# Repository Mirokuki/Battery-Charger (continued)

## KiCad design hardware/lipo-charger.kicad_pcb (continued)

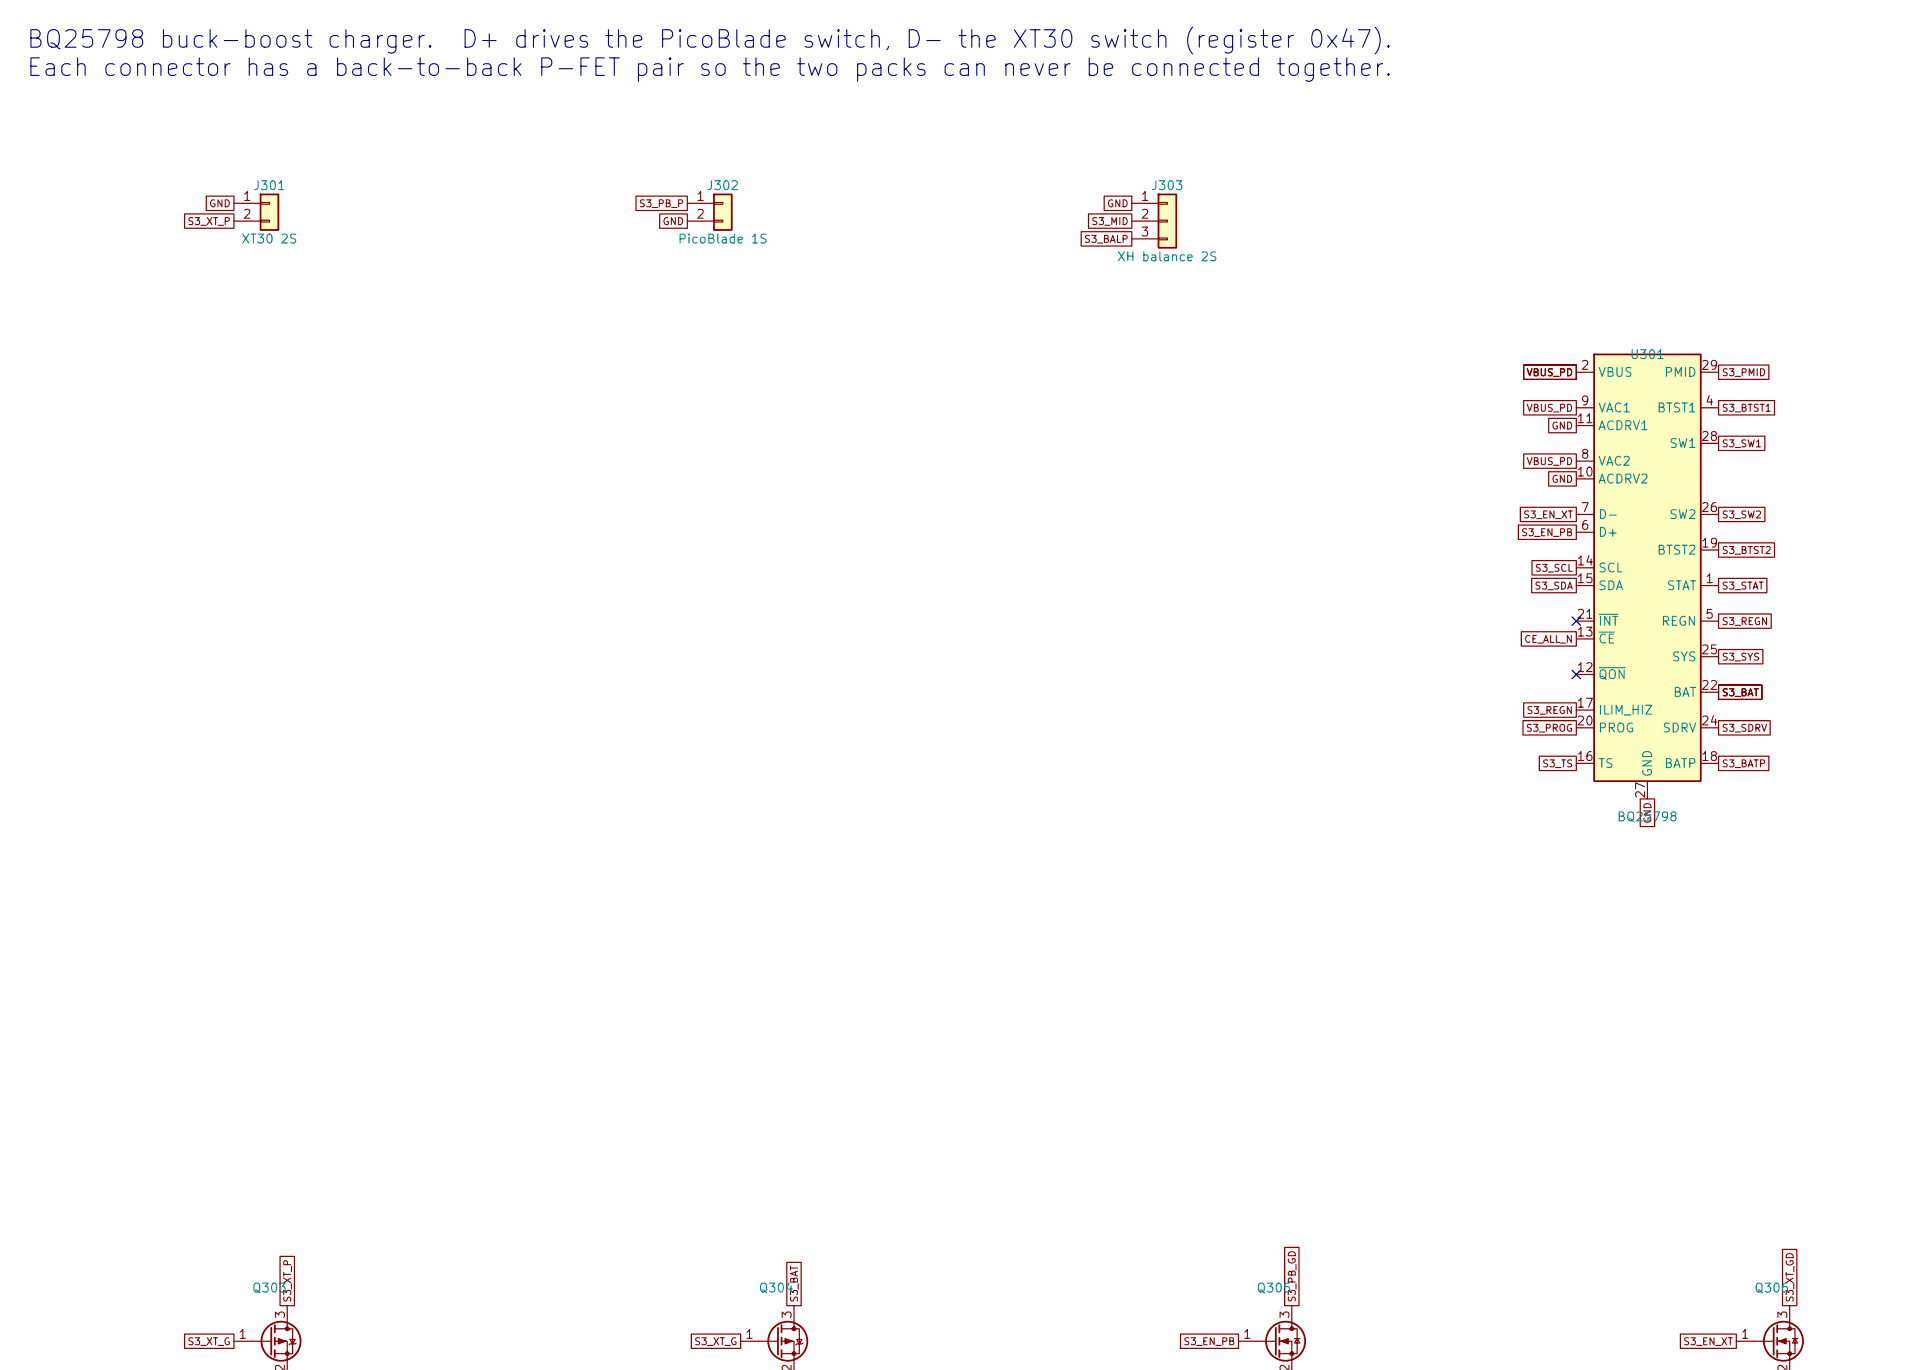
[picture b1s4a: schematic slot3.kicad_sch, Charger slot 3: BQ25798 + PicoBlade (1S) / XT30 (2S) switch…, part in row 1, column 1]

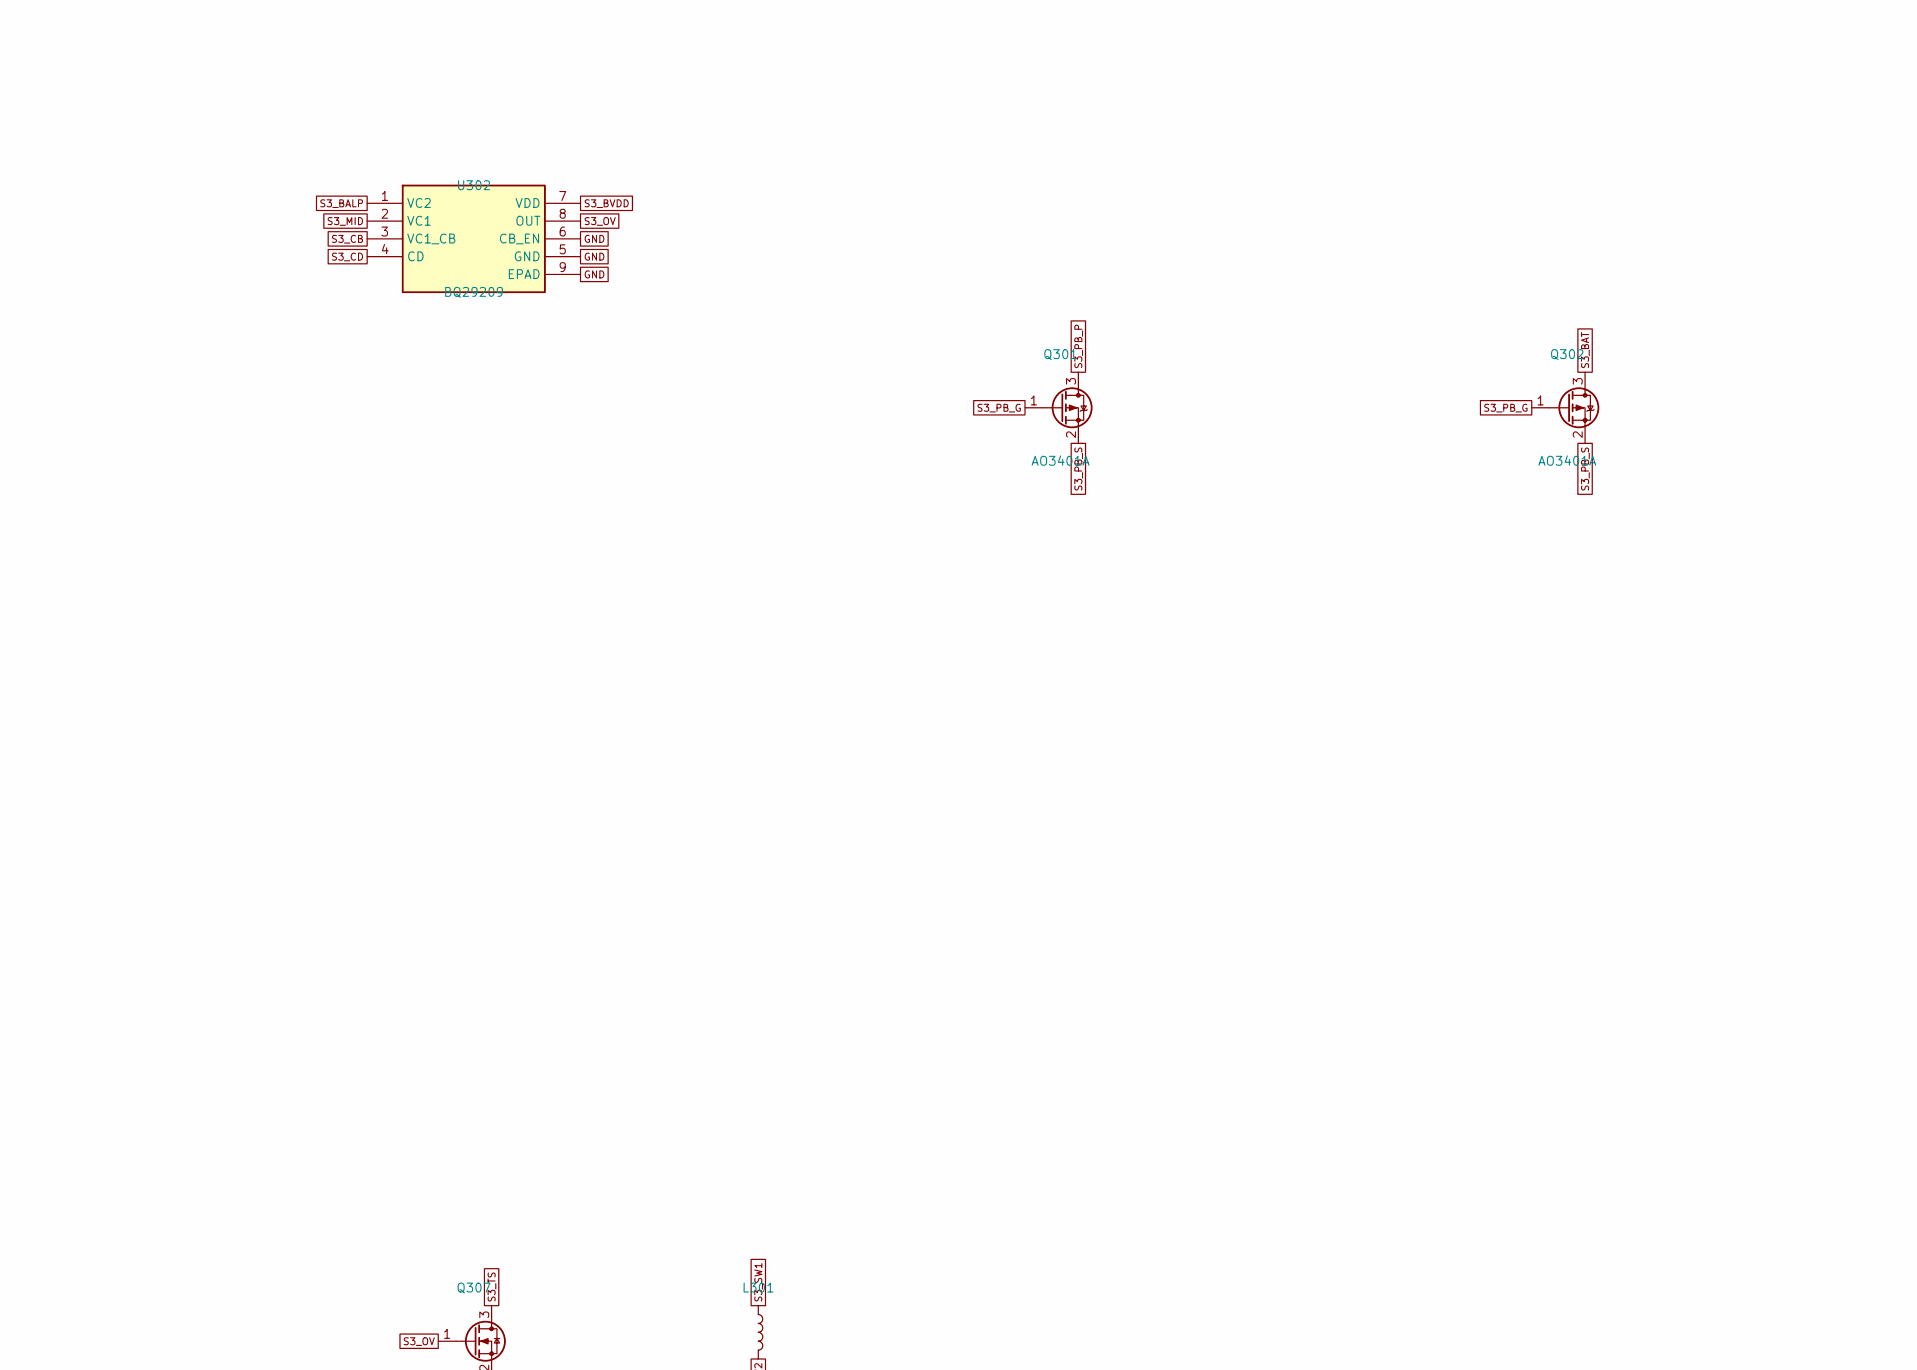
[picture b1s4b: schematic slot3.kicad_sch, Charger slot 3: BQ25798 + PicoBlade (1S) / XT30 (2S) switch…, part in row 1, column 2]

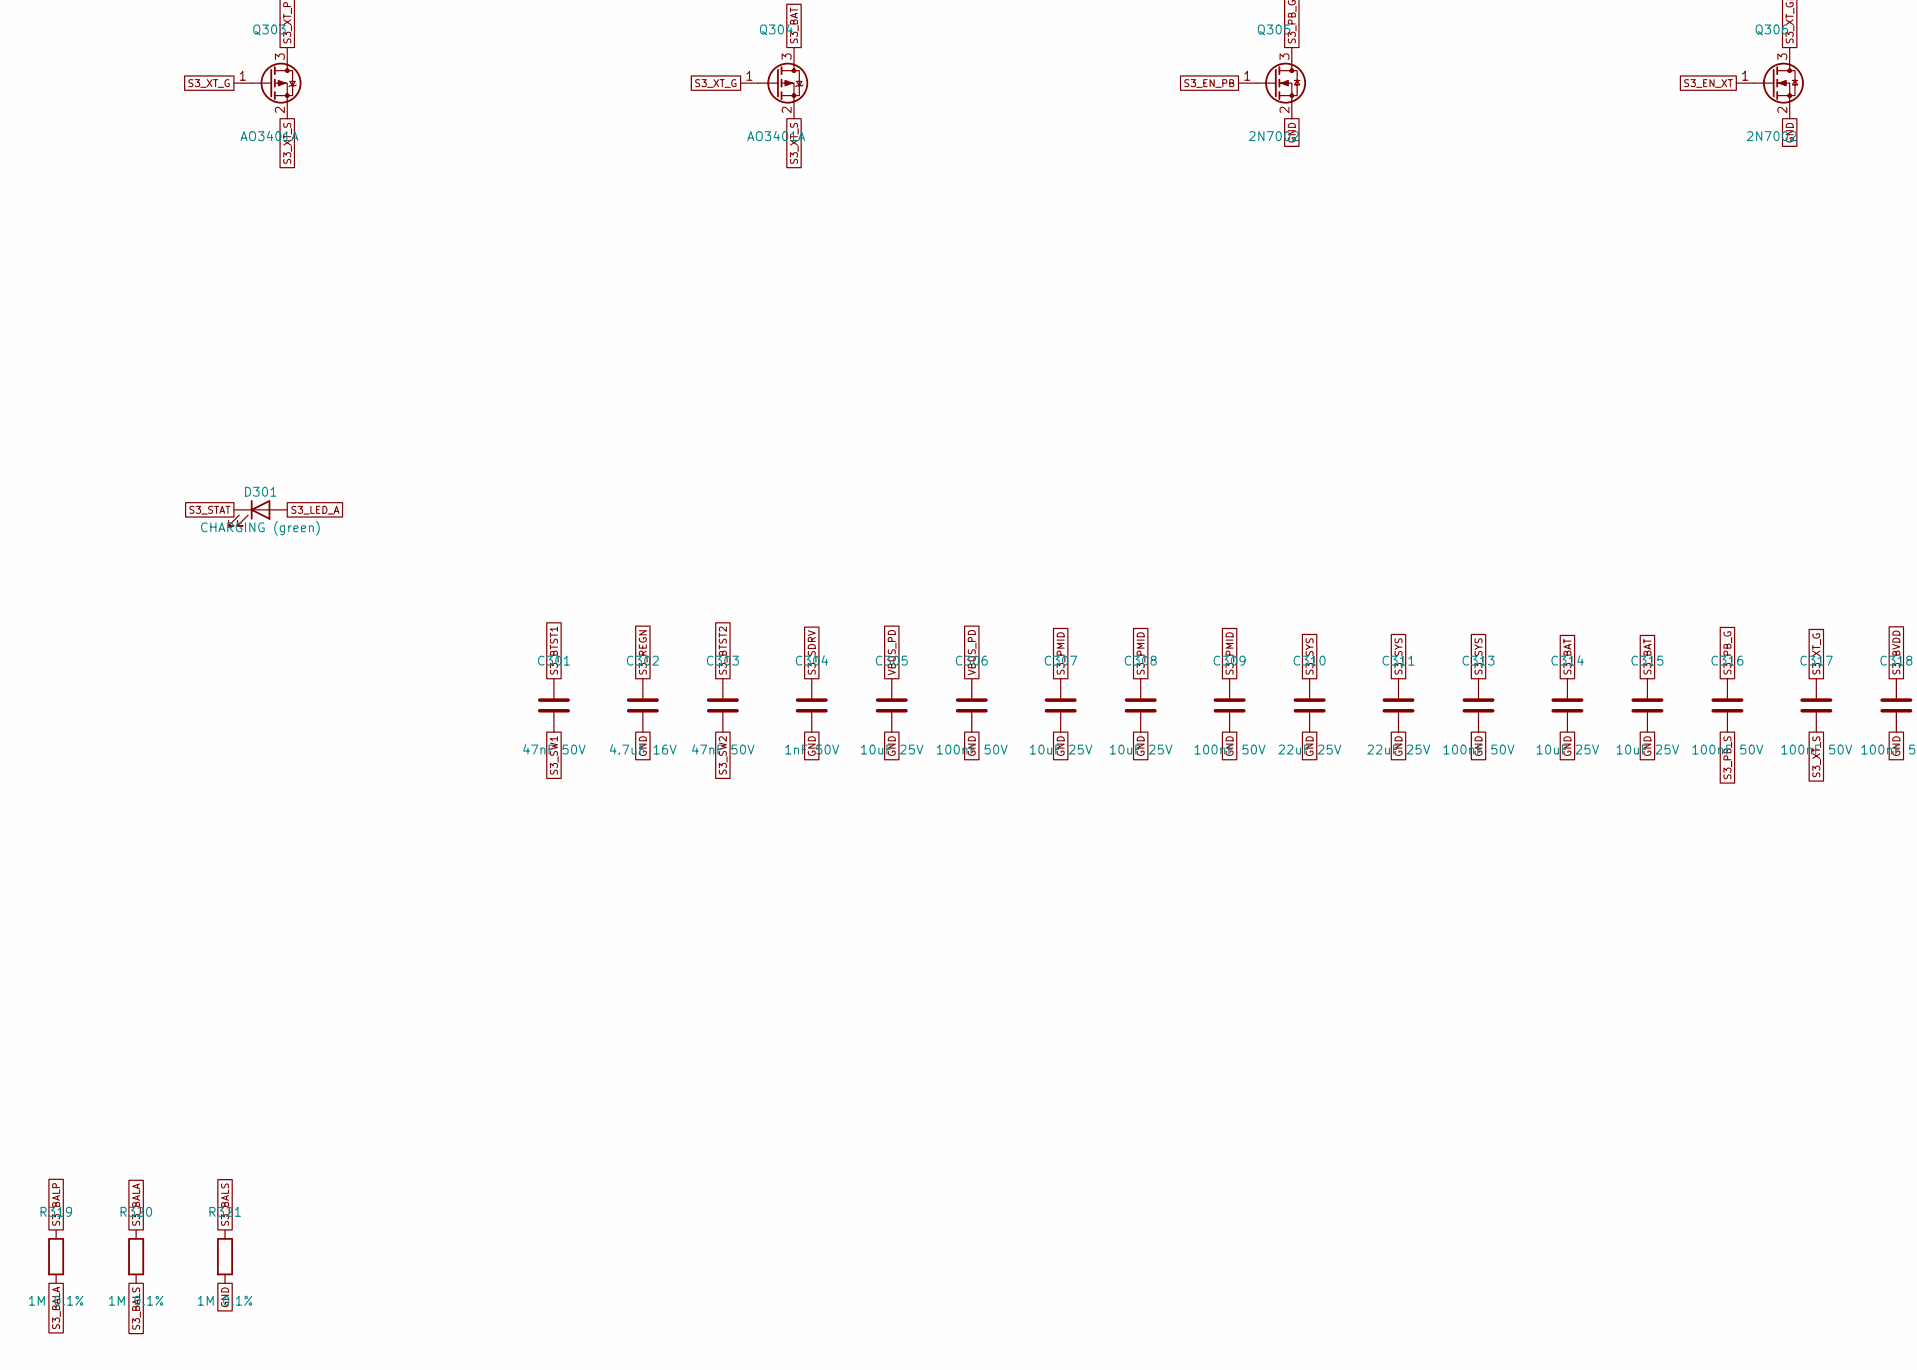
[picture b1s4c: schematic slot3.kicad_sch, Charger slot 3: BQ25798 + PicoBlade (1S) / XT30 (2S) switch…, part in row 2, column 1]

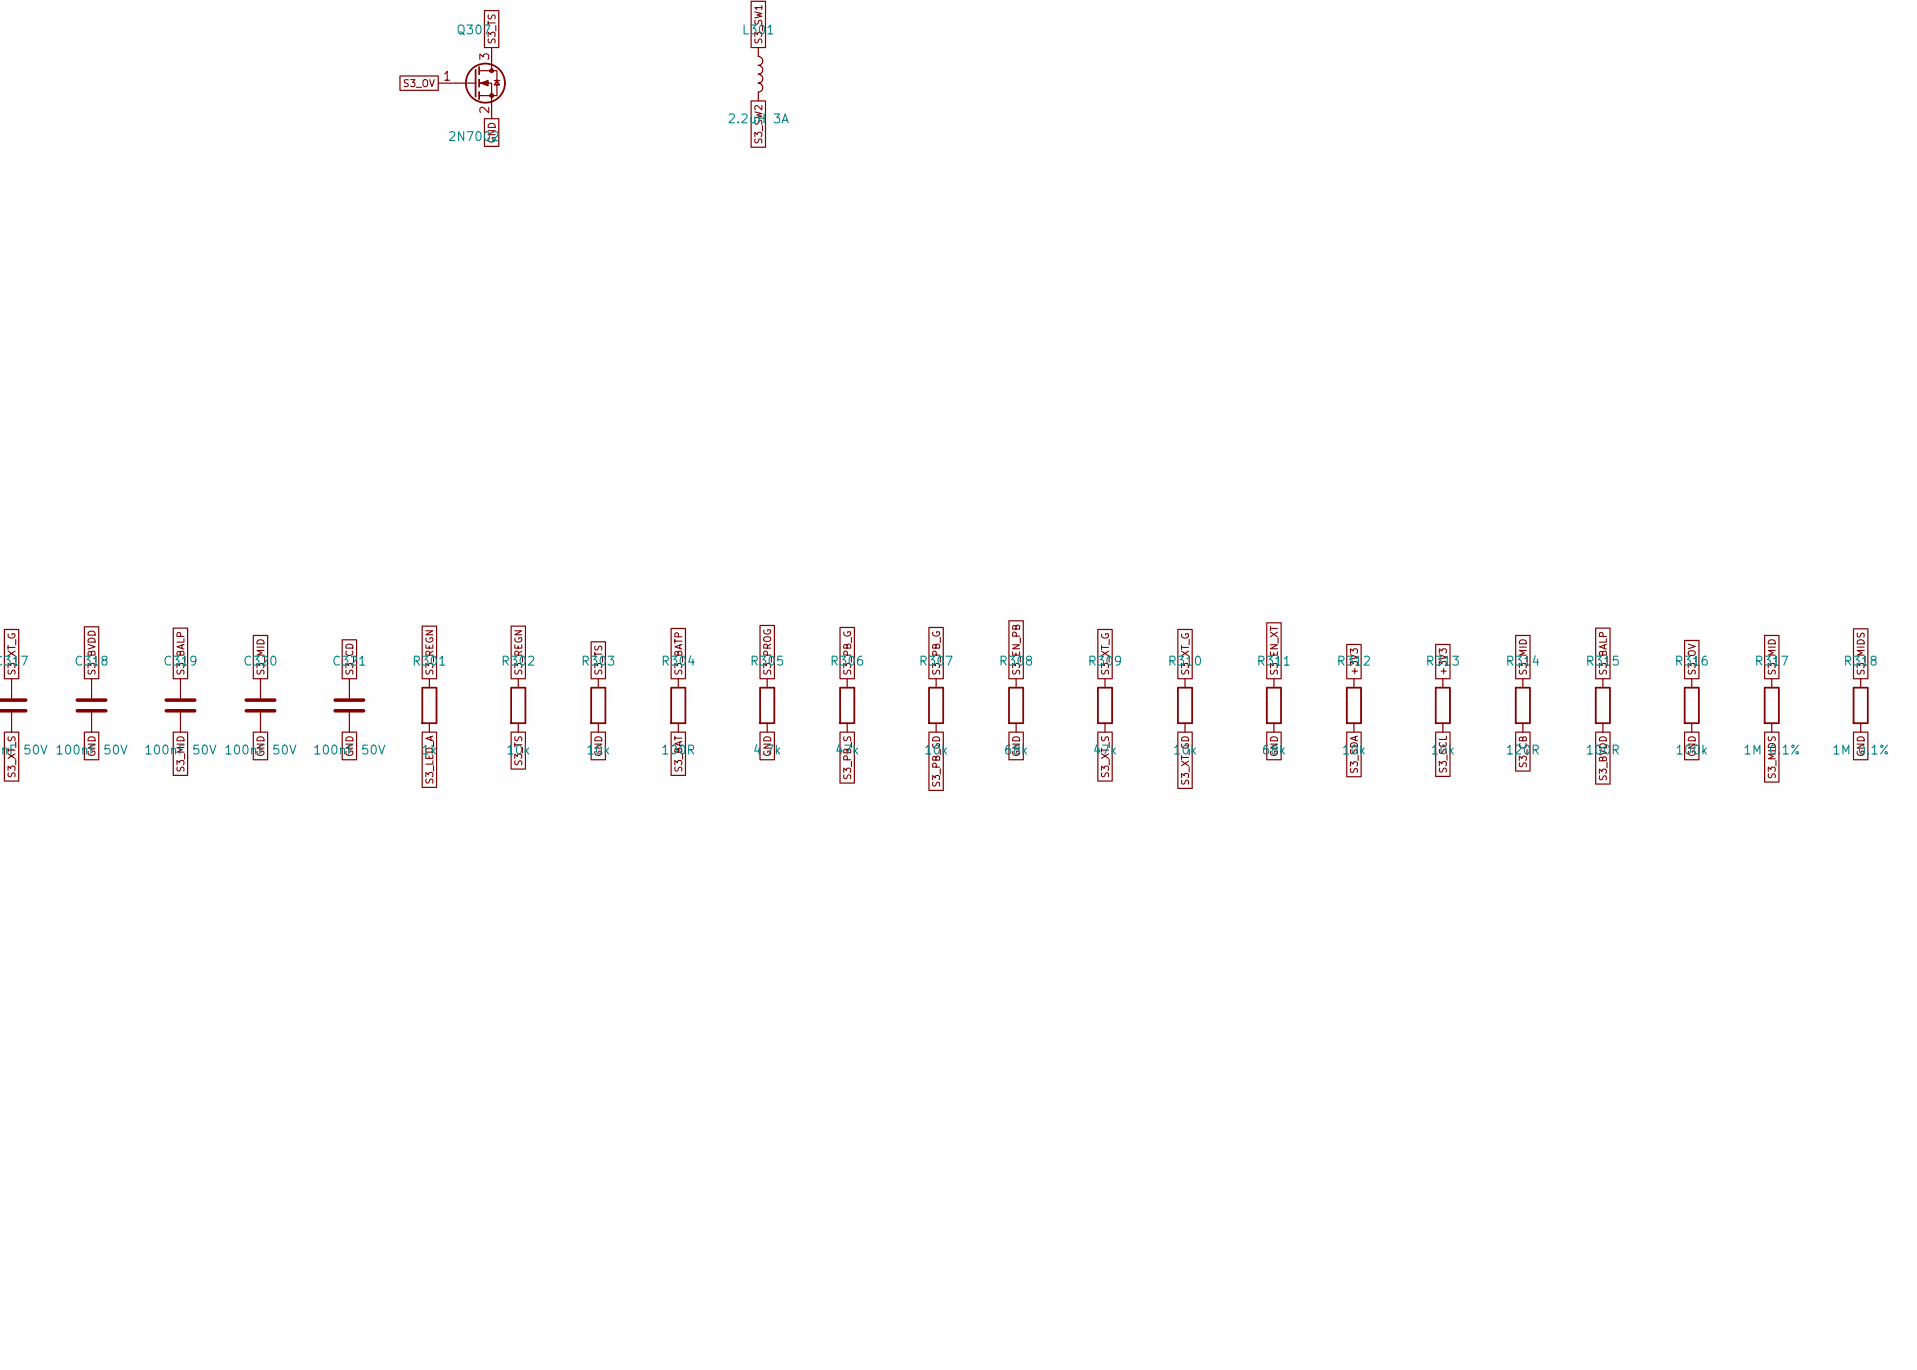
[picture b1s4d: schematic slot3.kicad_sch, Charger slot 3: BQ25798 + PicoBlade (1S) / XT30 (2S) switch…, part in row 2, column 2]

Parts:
C301, C303: 47nF 50V; C_0402_1005Metric; MPN CL05B473KB5NNNC
C302: 4.7uF 16V; C_0603_1608Metric; MPN CL10A475KO8NNNC; LCSC C19666
C304: 1nF 50V; C_0402_1005Metric; MPN CL05B102KB5NNNC; LCSC C1523
C305, C307, C308, C314, C315: 10uF 25V; C_0805_2012Metric; MPN CL21A106KAYNNNE; LCSC C15850
C306, C309, C313, C316, C317, C318, C319, C320, C321: 100nF 50V; C_0402_1005Metric; MPN CL05B104KB54PNC; LCSC C307331
C310, C311: 22uF 25V; C_0805_2012Metric; MPN CL21A226MAQNNNE; LCSC C45783
D301: CHARGING (green); LED_0603_1608Metric; MPN 19-217/GHC-YR1S2/3T; LCSC C72043
J301: XT30 2S; AMASS_XT30UPB-M_1x02_P5.0mm_Vertical; MPN XT30UPB-M; LCSC C99101
J302: PicoBlade 1S; Molex_PicoBlade_53047-0210_1x02_P1.25mm_Vertical; MPN 0530470210
J303: XH balance 2S; JST_XH_B3B-XH-A_1x03_P2.50mm_Vertical; MPN B3B-XH-A; LCSC C144394
L301: 2.2uH 3A; L_Changjiang_FNR4030S; MPN FNR4030S2R2MT
Q301, Q302, Q303, Q304: AO3401A; SOT-23; MPN AO3401A; LCSC C15127
Q305, Q306, Q307: 2N7002; SOT-23; MPN 2N7002; LCSC C8545
R301: 1k; R_0402_1005Metric; MPN 0402WGF1001TCE; LCSC C11702
R302, R303, R307, R310, R312, R313: 10k; R_0402_1005Metric; MPN 0402WGF1002TCE; LCSC C25744
R304, R315: 100R; R_0402_1005Metric; MPN 0402WGF1000TCE; LCSC C25076
R305: 4.7k; R_0402_1005Metric; MPN 0402WGF4701TCE; LCSC C25900
R306, R309: 47k; R_0402_1005Metric; MPN 0402WGF4702TCE; LCSC C25792
R308, R311: 68k; R_0402_1005Metric; MPN 0402WGF6802TCE; LCSC C36871
R314: 120R; R_0402_1005Metric; MPN 0402WGF1200TCE
R316: 100k; R_0402_1005Metric; MPN 0402WGF1003TCE; LCSC C25741
R317, R318, R319, R320, R321: 1M 0.1%; R_0402_1005Metric; MPN RT0402BRD071ML
U301: BQ25798; Texas_RQM0029A_VQFN-29_4x4mm_P0.4mm; MPN BQ25798RQMR; LCSC C2876768
U302: BQ29209; VSON-8-1EP_3x3mm_P0.65mm_EP1.65x2.4mm; MPN BQ29209DRBR

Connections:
+3V3: R312.1, R313.1; also elsewhere on the board
CE_ALL_N: U301.13 (~CE); also elsewhere on the board
GND: C302.2, C304.2, C305.2, C306.2, C307.2, C308.2, C309.2, C310.2, C311.2, C313.2, C314.2, C315.2, C318.2, C320.2, C321.2, J301.1, J302.2, J303.1, Q305.2 (S), Q306.2 (S), Q307.2 (S), R303.2, R305.2, R308.2, R311.2, R316.2, R318.2, R321.2, U301.10 (ACDRV2), U301.11 (ACDRV1), U301.27 (GND), U302.5 (GND), U302.6 (CB_EN), U302.9 (EPAD); also elsewhere on the board
S3_BALA: R319.2, R320.1
S3_BALP: C319.1, J303.3, R315.1, R319.1, U302.1 (VC2)
S3_BALS: R320.2, R321.1; also elsewhere on the board
S3_BAT: C314.1, C315.1, Q302.3 (D), Q304.3 (D), R304.2, U301.22 (BAT), U301.23 (BAT)
S3_BATP: R304.1, U301.18 (BATP)
S3_BTST1: C301.1, U301.4 (BTST1)
S3_BTST2: C303.1, U301.19 (BTST2)
S3_BVDD: C318.1, R315.2, U302.7 (VDD)
S3_CB: R314.2, U302.3 (VC1_CB)
S3_CD: C321.1, U302.4 (CD)
S3_EN_PB: Q305.1 (G), R308.1, U301.6 (D+)
S3_EN_XT: Q306.1 (G), R311.1, U301.7 (D-)
S3_LED_A: D301.2 (A), R301.2
S3_MID: C319.2, C320.1, J303.2, R314.1, R317.1, U302.2 (VC1)
S3_MIDS: R317.2, R318.1; also elsewhere on the board
S3_OV: Q307.1 (G), R316.1, U302.8 (OUT)
S3_PB_G: C316.1, Q301.1 (G), Q302.1 (G), R306.1, R307.1
S3_PB_GD: Q305.3 (D), R307.2
S3_PB_P: J302.1, Q301.3 (D)
S3_PB_S: C316.2, Q301.2 (S), Q302.2 (S), R306.2
S3_PMID: C307.1, C308.1, C309.1, U301.29 (PMID)
S3_PROG: R305.1, U301.20 (PROG)
S3_REGN: C302.1, R301.1, R302.1, U301.5 (REGN), U301.17 (ILIM_HIZ)
S3_SCL: R313.2, U301.14 (SCL); also elsewhere on the board
S3_SDA: R312.2, U301.15 (SDA); also elsewhere on the board
S3_SDRV: C304.1, U301.24 (SDRV)
S3_STAT: D301.1 (K), U301.1 (STAT)
S3_SW1: C301.2, L301.1, U301.28 (SW1)
S3_SW2: C303.2, L301.2, U301.26 (SW2)
S3_SYS: C310.1, C311.1, C313.1, U301.25 (SYS)
S3_TS: Q307.3 (D), R302.2, R303.1, U301.16 (TS)
S3_XT_G: C317.1, Q303.1 (G), Q304.1 (G), R309.1, R310.1
S3_XT_GD: Q306.3 (D), R310.2
S3_XT_P: J301.2, Q303.3 (D)
S3_XT_S: C317.2, Q303.2 (S), Q304.2 (S), R309.2
VBUS_PD: C305.1, C306.1, U301.2 (VBUS), U301.3 (VBUS), U301.8 (VAC2), U301.9 (VAC1); also elsewhere on the board

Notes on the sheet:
BQ25798 buck-boost charger. D+ drives the PicoBlade switch, D- the XT30 switch (register 0x47). Each connector has a back-to-back P-FET pair so the two packs can never be connected together.
